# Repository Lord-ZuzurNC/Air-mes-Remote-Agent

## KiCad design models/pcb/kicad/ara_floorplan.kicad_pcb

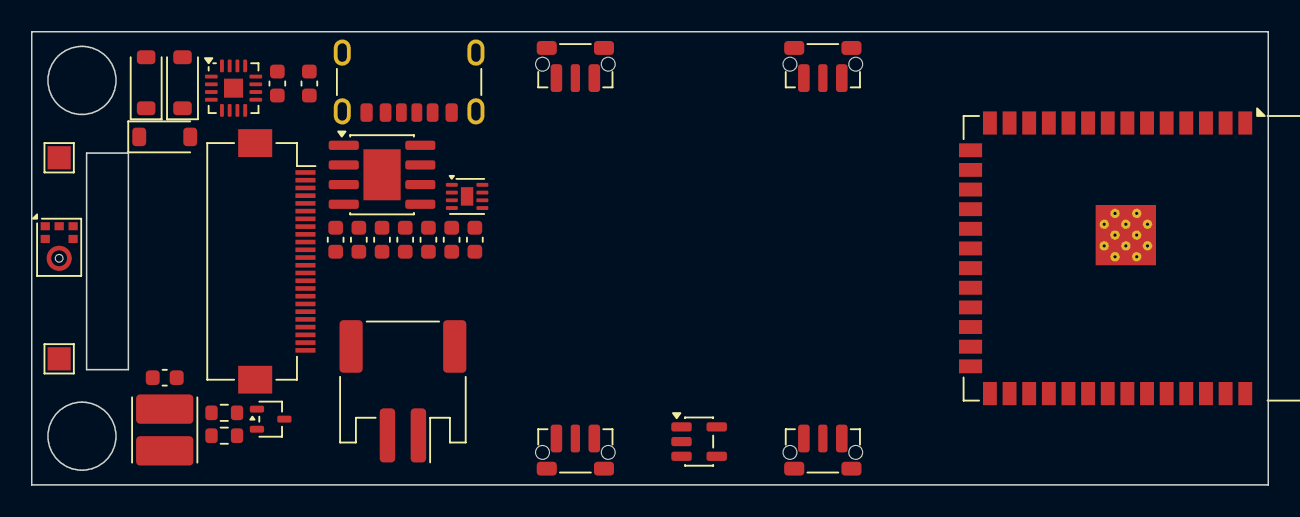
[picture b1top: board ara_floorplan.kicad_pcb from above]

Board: 2 copper layers, 80.0 x 29.3 mm, 32 parts (0 on the bottom side), 27 nets, no tracks yet.

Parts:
C2, C5, C6, C7, C9, C10, C11, C12: 1u 25V; C_0603_1608Metric
C3, C4: 4u7 25V; C_0603_1608Metric
D1, D2, D3: MBR0530T1G; D_SOD-123
J1: SHOU HAN TYPE-C 6P(073) on the GCT USB4125 land p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; USB_C_Receptacle_GCT_USB4125-xx-x_6P_TopMnt_Horizontal
J2: S2B-PH-SM4-TB; JST_PH_S2B-PH-SM4-TB_1x02-1MP_P2.00mm_Horizontal
J3: FH12A-24S-0.5SH(55) or FH12-24S-0.5SH(55); Hirose_FH12-24S-0.5SH_1x24-1MP_P0.50mm_Horizontal
L1: 47uH CKCS4030-47uH/M; L_Cenker_CKCS4030
MK1: ICS-43434; InvenSense_ICS-43434-6_3.5x2.65mm
Q1: Si1308EDL; SOT-323_SC-70
R1: 1M; R_0603_1608Metric
R2: 2R2; R_0603_1608Metric
SW1, SW2, SW3, SW4: SKRTLAE010; SW_Push_1P1T-MP_NO_Horizontal_Alps_SKRTLAE010
TP1: SPK+ wire pad; TestPoint_Pad_1.5x1.5mm
TP2: SPK- wire pad; TestPoint_Pad_1.5x1.5mm
U1: ESP32-S3-WROOM-1-N16R8; ESP32-S3-WROOM-1
U2: TP4056; SOIC-8-1EP_3.9x4.9mm_P1.27mm_EP2.41x3.3mm
U3: MAX17048G+T10; TDFN-8-1EP_2x2mm_P0.5mm_EP0.8x1.2mm
U4: MAX98357AETE+T; TQFN-16-1EP_3x3mm_P0.5mm_EP1.23x1.23mm
U5: AP2112K-3.3TRG1; SOT-23-5

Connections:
+3V3: C4.1, C6.1, J3.9, J3.10, L1.1, MK1.5, U1.2, U5.5
EPD_BUSY: J3.16, U1.17
EPD_CP: C3.2, D1.1, D2.2
EPD_CS: J3.13, U1.18
EPD_DC: J3.14, U1.21
EPD_GDR: J3.23, Q1.1, R1.1
EPD_MOSI: J3.11, U1.19
EPD_PREVGH: C5.1, D3.1, J3.4
EPD_PREVGL: C11.1, D1.2, J3.2
EPD_RESE: J3.22, Q1.2, R2.1
EPD_RST: J3.15, U1.22
EPD_SCK: J3.12, U1.20
EPD_SW: C3.1, D3.2, L1.2, Q1.3
EPD_VCOM: C12.1, J3.1
EPD_VDD: C7.1, J3.7
EPD_VSH1: C9.1, J3.5
EPD_VSH2: C2.1, J3.20
EPD_VSL: C10.1, J3.3
GND: C2.2, C4.2, C5.2, C6.2, C7.2, C9.2, C10.2, C11.2, C12.2, D2.1, J1.A12, J1.B12, J1.SH, J2.2, J3.8, J3.17, MK1.2, MK1.3, R1.2, R2.2, U1.1, U1.40, U1.41, U2.3, U2.9, U3.1, U3.4, U3.9, U4.3, U4.11, U4.15, U4.17, U5.2
I2S_BCLK: MK1.4, U1.4, U4.16
I2S_DIN: MK1.6, U1.7
I2S_DOUT: U1.6, U4.1
I2S_WS: MK1.1, U1.5, U4.14
SPK_N: TP2.1, U4.10
SPK_P: TP1.1, U4.9
VBAT: J2.1, U2.5, U3.2, U3.3, U4.7, U4.8, U5.1, U5.3
VBUS: J1.A9, J1.B9, U2.4, U2.8
